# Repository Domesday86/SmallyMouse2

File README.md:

## Synopsis

SmallyMouse2 is the AT90USB1287 firmware source code and KiCAD schematic/PCB design for the SmallyMouse2 project.

Detailed documentation is available on the [SmallyMouse2 wiki](https://github.com/domesday86/SmallyMouse2/wiki).

The schematic and PCB design in `KiCAD/` are in the KiCad 10 file format and require KiCad 10 or later to open. The original KiCad 4 files are available in the git history (commit `66cf90d` and earlier).

## Motivation

SmallyMouse2 is a project that creates a USB mouse adaptor for retro computers that use quadrature mouse input including the Acorn BBC Micro, Acorn Master series, Commodore Amiga, Atari ST, busmouse compatible computers and many more.  SmallyMouse2 provides both a generic mouse output header (for attaching mouse to retro computer cables) and an IDC connector suitable for use with Acorn 8-bit user-ports.  SmallyMouse2 also features a configurable quadrature rate limiter that prevents VIA overrun when in use with slower 8-bit machines.

SmallyMouse2 supports both JTAG and USB bootloader programming.  The AT90USB1287 is pre-programmed by Atmel with the (FLIP) DFU bootloader; this bootloader is recognised by Atmel Studio as a programming device and can be used to flash the firmware to the board.

## Installation

The firmware is built with the open-source AVR GNU toolchain (avr-gcc, avr-binutils, avr-libc) and CMake. A Nix flake supplies the complete, pinned toolchain along with the programming tools (avrdude for the Atmel-ICE, dfu-programmer for the USB bootloader).

### Building

Enter the firmware development shell (`code`, also the default) and build out-of-tree using a CMake preset:

    nix develop                     # or: nix develop .#code
    cmake --preset release          # or: cmake --preset debug
    cmake --build --preset release

The output is written to `build/release/`:

| File                | Use                                                                 |
|---------------------|---------------------------------------------------------------------|
| `SmallyMouse2.hex`  | Flash image (Intel HEX) - JTAG via avrdude, DFU via dfu-programmer  |
| `SmallyMouse2-with-bootloader.hex` | Firmware merged with the LUFA DFU bootloader - JTAG via avrdude |
| `SmallyMouse2.elf`  | Full image with symbols - JTAG via Microchip Studio / debugging     |
| `SmallyMouse2.eep`  | EEPROM image (currently empty)                                      |
| `SmallyMouse2.srec` | Flash image (Motorola S-record)                                     |
| `SmallyMouse2.lss`  | Extended listing                                                    |
| `SmallyMouse2.map`  | Linker map                                                          |

Two firmware images are built from the same source. `SmallyMouse2` is the normal firmware; `SmallyMouse2-swapped` has the middle and right mouse buttons reversed (for example, for Kensington Expert Mouse trackballs used as replacements for the Domesday AIV system's RB2 trackball). Each image has the same set of files, so `SmallyMouse2-swapped.hex`, `SmallyMouse2-swapped-with-bootloader.hex`, and so on, sit next to the files above.

Alternatively `nix build` produces the same files in `./result/` without entering a shell.

Without Nix, any avr-gcc toolchain, CMake 3.24+ and Ninja on the `PATH` will work with the same commands.

### Programming via JTAG (Atmel-ICE)

Connect the Atmel-ICE to the JTAG header, then:

    cmake --build --preset release --target flash-jtag

or, without a build tree, `nix run .#flash-jtag`. The fuses and lock bits can be read with the `read-fuses-jtag` target.

To flash the firmware with the middle and right buttons swapped, use `flash-jtag-swapped` (or `nix run .#flash-jtag-swapped`) instead.

Programming over JTAG performs a chip erase, which also removes the DFU bootloader, so `flash-jtag` writes `SmallyMouse2-with-bootloader.hex` (the firmware merged with the LUFA DFU bootloader) and the board can still be updated over USB afterwards. The bootloader image comes from the Nix flake; without it (`BOOTLOADER_HEX` unset) `flash-jtag` writes the firmware alone and the bootloader is lost.

### Restoring the DFU bootloader and fuses (Atmel-ICE)

If the bootloader is missing (for example after programming with another tool) or the fuses no longer select it, connect the Atmel-ICE and run:

    nix run .#flash-bootloader-jtag

or, from the dev shell, `cmake --build --preset release --target flash-bootloader-jtag`. This builds the LUFA DFU bootloader from the pinned LUFA source, erases the chip, writes the bootloader and sets the high/extended fuses to the factory values (`hfuse 0x99`, `efuse 0xF3`: 8 KB boot section, JTAG enabled, HWB bootloader entry enabled). The LUFA bootloader uses the same USB ID as the factory one, so the DFU steps below work unchanged. Any application firmware is removed; reprogram it over USB afterwards.

### Programming via USB (DFU bootloader)

Put the AT90USB1287 into its factory DFU bootloader (hold HWB low while resetting), then:

    cmake --build --preset release --target flash-dfu

or `nix run .#flash-dfu`. The device is erased, programmed and then started.

To flash the firmware with the middle and right buttons swapped, use `flash-dfu-swapped` (or `nix run .#flash-dfu-swapped`) instead.

### USB permissions (udev)

On Linux, programming as a normal user needs udev rules for two devices:

| Device                        | USB ID      | Used by        |
|-------------------------------|-------------|----------------|
| Atmel-ICE                     | `03eb:2141` | avrdude        |
| AT90USB1287 DFU bootloader    | `03eb:2ffb` | dfu-programmer |

The Atmel-ICE needs two rules. avrdude can reach it through libusb or through hidapi, and each uses a different device node (`usb` and `hidraw`).

On NixOS, add the rules to your system configuration:

```nix
services.udev.extraRules = ''
  # Atmel-ICE (AVR JTAG programmer) - usb node for libusb, hidraw node for hidapi
  SUBSYSTEM=="usb", ATTRS{idVendor}=="03eb", ATTRS{idProduct}=="2141", MODE="660", GROUP="users"
  SUBSYSTEM=="hidraw", ATTRS{idVendor}=="03eb", ATTRS{idProduct}=="2141", MODE="660", GROUP="users"
  # AT90USB1287 DFU bootloader
  SUBSYSTEM=="usb", ATTRS{idVendor}=="03eb", ATTRS{idProduct}=="2ffb", MODE="660", GROUP="users"
'';
```

On other distributions, put the same three lines in a file such as `/etc/udev/rules.d/70-smallymouse2.rules`. Make sure your user is in the group the rules name, or change `GROUP` to one it is in (for example `plugdev` on Debian and Ubuntu). Then reload the rules with `sudo udevadm control --reload-rules`.

On either system, unplug and replug the device after adding the rules.

## Case

`Case/` holds an OpenSCAD case design, built with the [BOSL2](https://github.com/BelfrySCAD/BOSL2) library:

| File        | Contents                                                                           |
|-------------|------------------------------------------------------------------------------------|
| `pcb.scad`  | Dimensional model of the assembled board, built from the footprint placements in `KiCAD/SmallyMouse2.kicad_pcb`, with helpers giving the board-space position of any part by reference (for example `pcb_part_box("P1")` for the USB connector) |
| `case.scad` | Two-part case (base and lid) positioned against the board model                   |

### Opening the design

From the repository root, enter the `openscad` dev shell and open the case:

    nix develop .#openscad
    openscad Case/case.scad

Start OpenSCAD from inside the dev shell: the shell sets `OPENSCADPATH` to the pinned BOSL2, so `include <BOSL2/std.scad>` fails if OpenSCAD is started any other way (for example from the desktop menu). `openscad Case/pcb.scad` opens the board model on its own.

Open the Customizer (Window → Customizer) and set `part` to choose what is shown:

| `part`     | Shows                                                                    |
|------------|--------------------------------------------------------------------------|
| `assembly` | Base, board and a transparent lid together; raise `explode` to lift the lid |
| `base`     | The base alone, laid out for printing                                    |
| `lid`      | The lid alone, turned over for printing                                  |
| `pcb`      | The board alone                                                          |

The case dimensions (wall thickness, clearances, standoff height and so on) are in the same panel.

F5 gives a fast preview; F6 does the full render needed before exporting an STL with F7.

### Exporting STLs

Without the GUI, `nix build .#case` renders `case-base.stl`, `case-lid.stl` and `case-pcb.stl` into `./result/`. A single part can be exported from the dev shell with, for example:

    openscad -o case-lid.stl -D 'part="lid"' Case/case.scad

Component heights that are not in the KiCad data (the USB connector, IDC header and pin headers) use typical datasheet values, set near the top of `pcb.scad`; check them against the parts fitted before printing.

## Author

SmallyMouse2 is written and maintained by Simon Inns.

## License (Software)

    SmallyMouse2 is free software: you can redistribute it and/or modify
    it under the terms of the GNU General Public License as published by
    the Free Software Foundation, either version 3 of the License, or
    (at your option) any later version.

    SmallyMouse2 is distributed in the hope that it will be useful,
    but WITHOUT ANY WARRANTY; without even the implied warranty of
    MERCHANTABILITY or FITNESS FOR A PARTICULAR PURPOSE.  See the
    GNU General Public License for more details.

    You should have received a copy of the GNU General Public License
    along with SmallyMouse2. If not, see <http://www.gnu.org/licenses/>.

## License (Hardware)

Both the schematic and the PCB design of SmallyMouse2 (i.e. the KiCAD project and files) are covered by a Creative Commons license; as with the software you are welcome (and encouraged!) to extend, re-spin and otherwise use and modify the design as allowed by the license.  However; under the terms of the Attribution-ShareAlike 4.0 International (CC BY-SA 4.0) license you are required to release your design (or redesign) under the same license.  For details of the licensing requirements please see <https://creativecommons.org/licenses/by-sa/4.0/>

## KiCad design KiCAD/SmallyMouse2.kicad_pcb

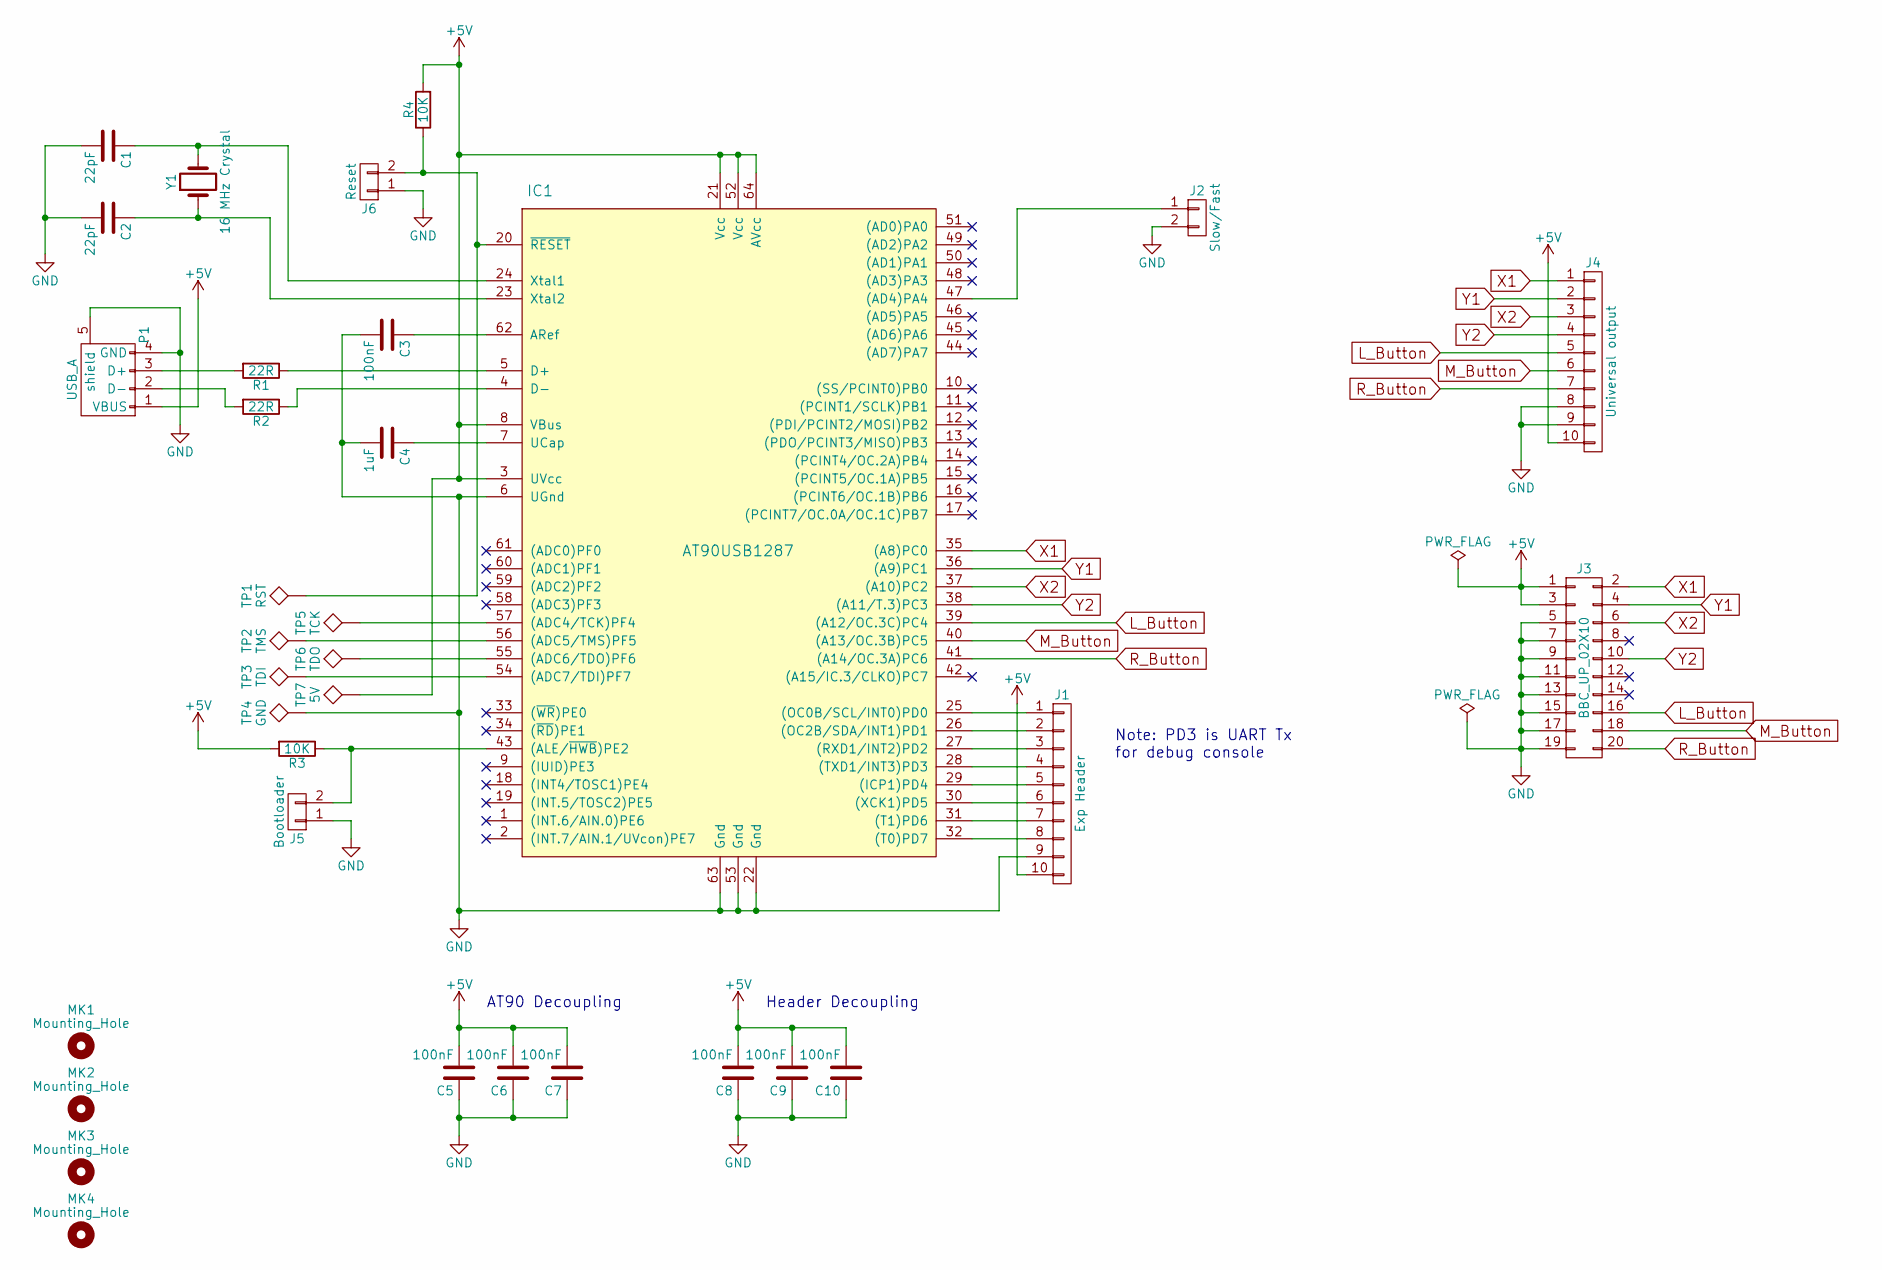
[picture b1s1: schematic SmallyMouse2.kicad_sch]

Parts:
C1, C2: 22pF; C_0805_HandSoldering
C3, C5, C6, C7, C8, C9, C10: 100nF; C_0805_HandSoldering
C4: 1uF; C_0805_HandSoldering
IC1: AT90USB1287; TQFP-64_14x14mm_Pitch0.8mm
J1: Exp Header; Pin_Header_Straight_1x10_Pitch2.54mm
J2: Slow/Fast; Pin_Header_Straight_1x02_Pitch2.54mm
J3: BBC_UP_02X10; IDC_Header_Straight_20pins
J4: Universal output; Pin_Header_Straight_1x10_Pitch2.54mm
J5: Bootloader; Pin_Header_Straight_1x02_Pitch2.54mm
J6: Reset; Pin_Header_Straight_1x02_Pitch2.54mm
MK1, MK2, MK3, MK4: Mounting_Hole; MountingHole_3.2mm_M3_ISO14580
P1: USB_A; Amphenol_87583-2010BLF
R1, R2: 22R; R_0805_HandSoldering
R3, R4: 10K; R_0805_HandSoldering
TP1: RST; Measurement_Point_Square-SMD-Pad_Small
TP2: TMS; Measurement_Point_Square-SMD-Pad_Small
TP3: TDI; Measurement_Point_Square-SMD-Pad_Small
TP4: GND; Measurement_Point_Square-SMD-Pad_Small
TP5: TCK; Measurement_Point_Square-SMD-Pad_Small
TP6: TDO; Measurement_Point_Square-SMD-Pad_Small
TP7: 5V; Measurement_Point_Square-SMD-Pad_Small
Y1: 16 MHz Crystal; Crystal_SMD_5032-2pin_5.0x3.2mm_HandSoldering

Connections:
+5V: C5.2, C6.2, C7.2, C8.2, C9.2, C10.2, IC1.3 (UVcc), IC1.8 (VBus), IC1.21 (Vcc), IC1.52 (Vcc), IC1.64 (AVcc), J1.10, J3.1, J3.3, J4.10, P1.1 (VBUS), R3.2, R4.2, TP7.1 (~_1)
GND: C1.2, C2.2, C3.2, C4.2, C5.1, C6.1, C7.1, C8.1, C9.1, C10.1, IC1.6 (UGnd), IC1.22 (Gnd), IC1.53 (Gnd), IC1.63 (Gnd), J1.9, J2.2, J3.5, J3.7, J3.9, J3.11, J3.13, J3.15, J3.17, J3.19, J4.8, J4.9, J5.1, J6.1, P1.4 (GND), P1.5 (shield), TP4.1 (~_1)
L_Button: IC1.39 ((A12/OC.3C)PC4), J3.16, J4.5
M_Button: IC1.40 ((A13/OC.3B)PC5), J3.18, J4.6
unnamed: IC1.47 ((AD4)PA4), J2.1
unnamed: IC1.57 ((ADC4/TCK)PF4), TP5.1 (~_1)
unnamed: IC1.56 ((ADC5/TMS)PF5), TP2.1 (~_1)
unnamed: IC1.55 ((ADC6/TDO)PF6), TP6.1 (~_1)
unnamed: IC1.54 ((ADC7/TDI)PF7), TP3.1 (~_1)
unnamed: IC1.43 ((ALE/~HWB)PE2), J5.2, R3.1
unnamed: IC1.29 ((ICP1)PD4), J1.5
unnamed: IC1.25 ((OC0B/SCL/INT0)PD0), J1.1
unnamed: IC1.26 ((OC2B/SDA/INT1)PD1), J1.2
unnamed: IC1.27 ((RXD1/INT2)PD2), J1.3
unnamed: IC1.32 ((T0)PD7), J1.8
unnamed: IC1.31 ((T1)PD6), J1.7
unnamed: IC1.28 ((TXD1/INT3)PD3), J1.4
unnamed: IC1.30 ((XCK1)PD5), J1.6
unnamed: C3.1, IC1.62 (ARef)
unnamed: IC1.5 (D+), R1.1
unnamed: IC1.4 (D-), R2.1
unnamed: C4.1, IC1.7 (UCap)
unnamed: C1.1, IC1.24 (Xtal1), Y1.2
unnamed: C2.1, IC1.23 (Xtal2), Y1.1
unnamed: IC1.20 (~RESET), J6.2, R4.1, TP1.1 (~_1)
unnamed: P1.3 (D+), R1.2
unnamed: P1.2 (D-), R2.2
R_Button: IC1.41 ((A14/OC.3A)PC6), J3.20, J4.7
X1: IC1.35 ((A8)PC0), J3.2, J4.1
X2: IC1.37 ((A10)PC2), J3.6, J4.3
Y1: IC1.36 ((A9)PC1), J3.4, J4.2
Y2: IC1.38 ((A11/T.3)PC3), J3.10, J4.4

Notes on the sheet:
AT90 Decoupling
Note: PD3 is UART Tx for debug console
Header Decoupling

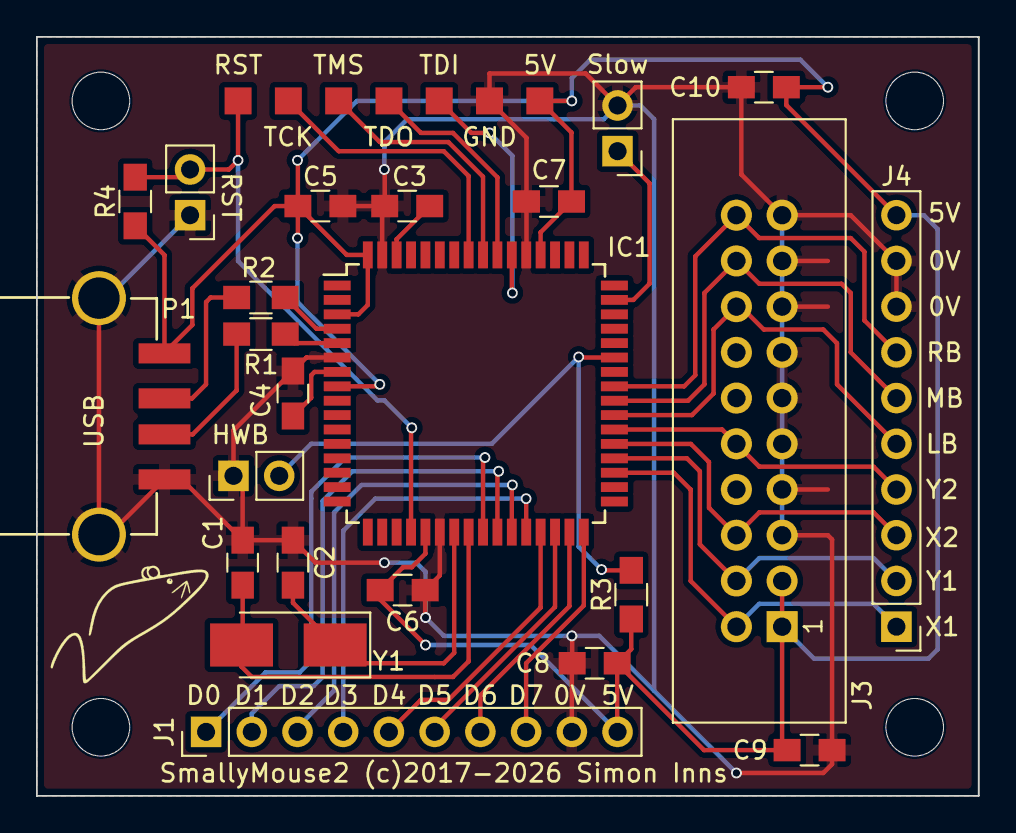
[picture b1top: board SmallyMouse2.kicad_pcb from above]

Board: 2 copper layers, 52.3 x 42.2 mm, 34 parts (0 on the bottom side), 32 nets.

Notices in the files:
KiCAD/SmallyMouse2.kicad_pcb:
(c)2017 Simon Inns
License: Attribution-ShareAlike 4.0 International (CC BY-SA 4.0)
SmallyMouse2 (c)2017-2026 Simon Inns
